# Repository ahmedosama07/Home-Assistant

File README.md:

# Home-Assistant
ESP32 based Smart Home Assistant

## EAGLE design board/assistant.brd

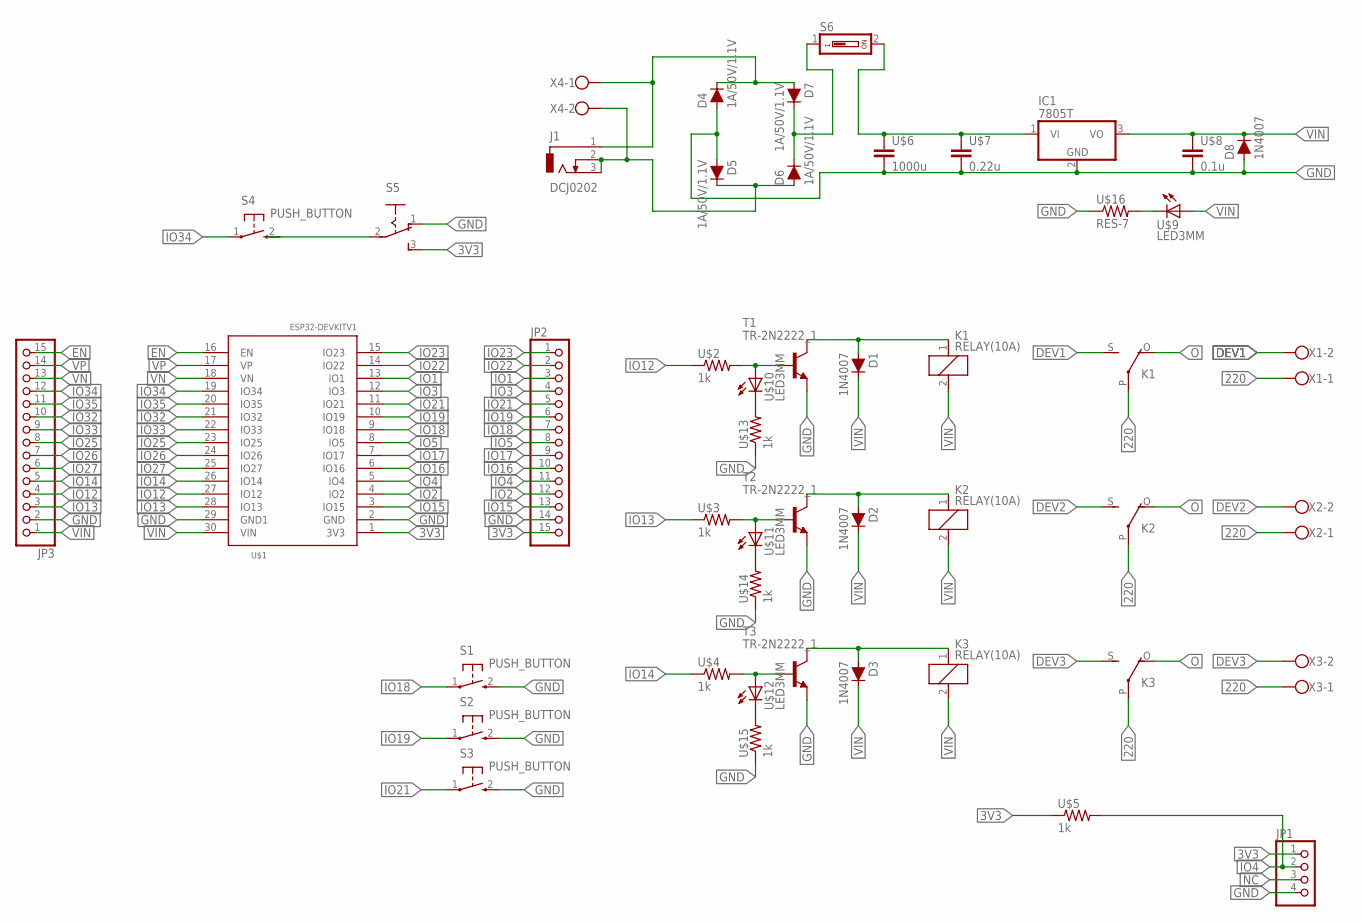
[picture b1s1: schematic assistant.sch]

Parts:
D1, D2, D3, D8: 1N4007; DIODE-1N4001
D4, D5, D6, D7: 1A/50V/1.1V; DIODE-1N4001
IC1: 7805T; TO220H
J1: DCJ0202
JP1: PINHD-1X4; 1X04
JP2, JP3: PINHD-1X15; 1X15
K1, K2, K3: RELAY(10A); G5LE
S1, S2, S3, S4: PUSH_BUTTON; B3F-10XX
S5: SLIDING_SWITCH; 255SB
S6: DS01; DS-01
T1, T2, T3: TR-2N2222_1; TO92-EBC
U$1: ESP32DEVKITV1; ESP32-DEVKITV1
U$2, U$3, U$4, U$5, U$13, U$14, U$15: 1k; 0204/7
U$6: 1000u; C025-025X050
U$7: 0.22u; C025-025X050
U$8: 0.1u; C025-025X050
U$9, U$10, U$11, U$12: LED3MM
U$16: RES-7; 0204/7
X1, X2, X3, X4: ROSTA.POWER; W239-302

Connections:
3V3: JP1.1, JP2.15, S5.3 (S), U$1.1 (3V3), U$5.1
220: K1.P, K2.P, K3.P, X1.1, X2.1, X3.1
DEV1: K1.S, X1.2
DEV2: K2.S, X2.2
DEV3: K3.S, X3.2
EN: JP3.15, U$1.16 (EN)
GND: D4.A, D5.A, D8.A, IC1.2 (GND), JP1.4, JP2.14, JP3.2, S1.2 (S), S2.2 (S), S3.2 (S), S5.1 (O), T1.E, T2.E, T3.E, U$1.2 (GND), U$1.29 (GND1), U$6.2, U$7.2, U$8.2, U$13.1, U$14.1, U$15.1, U$16.1
IO1: JP2.3, U$1.13 (IO1)
IO2: JP2.12, U$1.4 (IO2)
IO3: JP2.4, U$1.12 (IO3)
IO4: JP1.2, JP2.11, U$1.5 (IO4), U$5.2
IO5: JP2.8, U$1.8 (IO5)
IO12: JP3.4, U$1.27 (IO12), U$2.1
IO13: JP3.3, U$1.28 (IO13), U$3.1
IO14: JP3.5, U$1.26 (IO14), U$4.1
IO15: JP2.13, U$1.3 (IO15)
IO16: JP2.10, U$1.6 (IO16)
IO17: JP2.9, U$1.7 (IO17)
IO18: JP2.7, S1.1, U$1.9 (IO18)
IO19: JP2.6, S2.1, U$1.10 (IO19)
IO21: JP2.5, S3.1, U$1.11 (IO21)
IO22: JP2.2, U$1.14 (IO22)
IO23: JP2.1, U$1.15 (IO23)
IO25: JP3.8, U$1.23 (IO25)
IO26: JP3.7, U$1.24 (IO26)
IO27: JP3.6, U$1.25 (IO27)
IO32: JP3.10, U$1.21 (IO32)
IO33: JP3.9, U$1.22 (IO33)
IO34: JP3.12, S4.1, U$1.19 (IO34)
IO35: JP3.11, U$1.20 (IO35)
unnamed: T1.B, U$2.2, U$10.A
unnamed: D1.A, K1.1, T1.C
unnamed: T2.B, U$3.2, U$11.A
unnamed: D2.A, K2.1, T2.C
unnamed: T3.B, U$4.2, U$12.A
unnamed: D3.A, K3.1, T3.C
unnamed: D5.C, D6.A, J1.2, J1.3, X4.2
unnamed: S4.2 (S), S5.2
unnamed: D4.C, D7.A, J1.1, X4.1
unnamed: U$10.K (C), U$13.2
unnamed: U$11.K (C), U$14.2
unnamed: IC1.1 (VI), S6.2, U$6.1, U$7.1
unnamed: U$12.K (C), U$15.2
unnamed: U$9.K (C), U$16.2
unnamed: D6.C, D7.C, S6.1
NC: JP1.3
O: K1.O, K2.O, K3.O
VIN: D1.C, D2.C, D3.C, D8.C, IC1.3 (VO), JP3.1, K1.2, K2.2, K3.2, U$1.30 (VIN), U$8.1, U$9.A
VN: JP3.13, U$1.18 (VN)
VP: JP3.14, U$1.17 (VP)

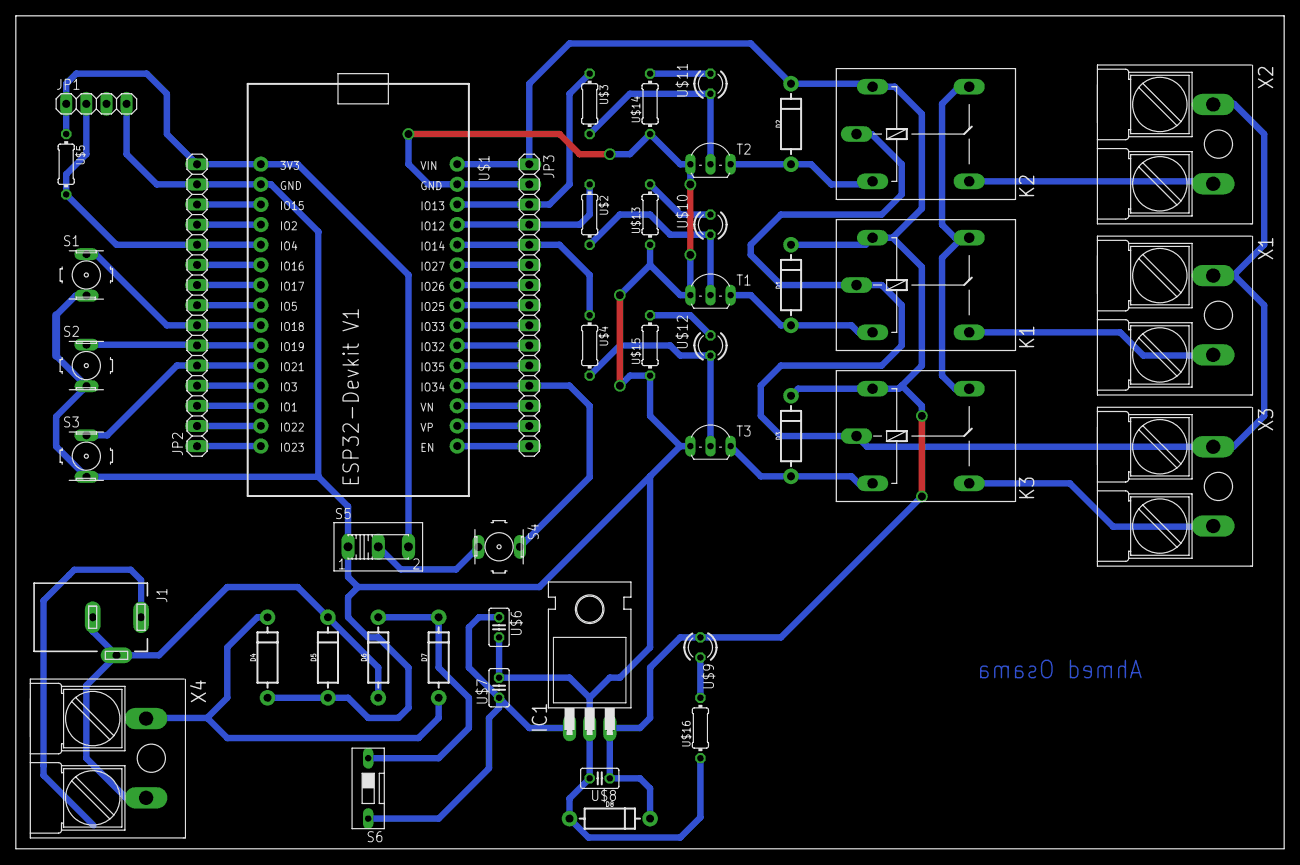
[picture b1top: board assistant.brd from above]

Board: 2 copper layers, 160.0 x 105.1 mm, 45 parts (0 on the bottom side), 49 nets.

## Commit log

2023-10-22 OTA added
2023-10-23 Blynk based
2023-10-24 board
2023-10-25 prepare for PR
2023-10-25 Revert "prepare for PR"
    This reverts commit 7d51d358836929c6c11cbe6c9874093410d4237c.
2023-10-25 V2 sinric with our own ESP32 manager
2023-10-25 final board
